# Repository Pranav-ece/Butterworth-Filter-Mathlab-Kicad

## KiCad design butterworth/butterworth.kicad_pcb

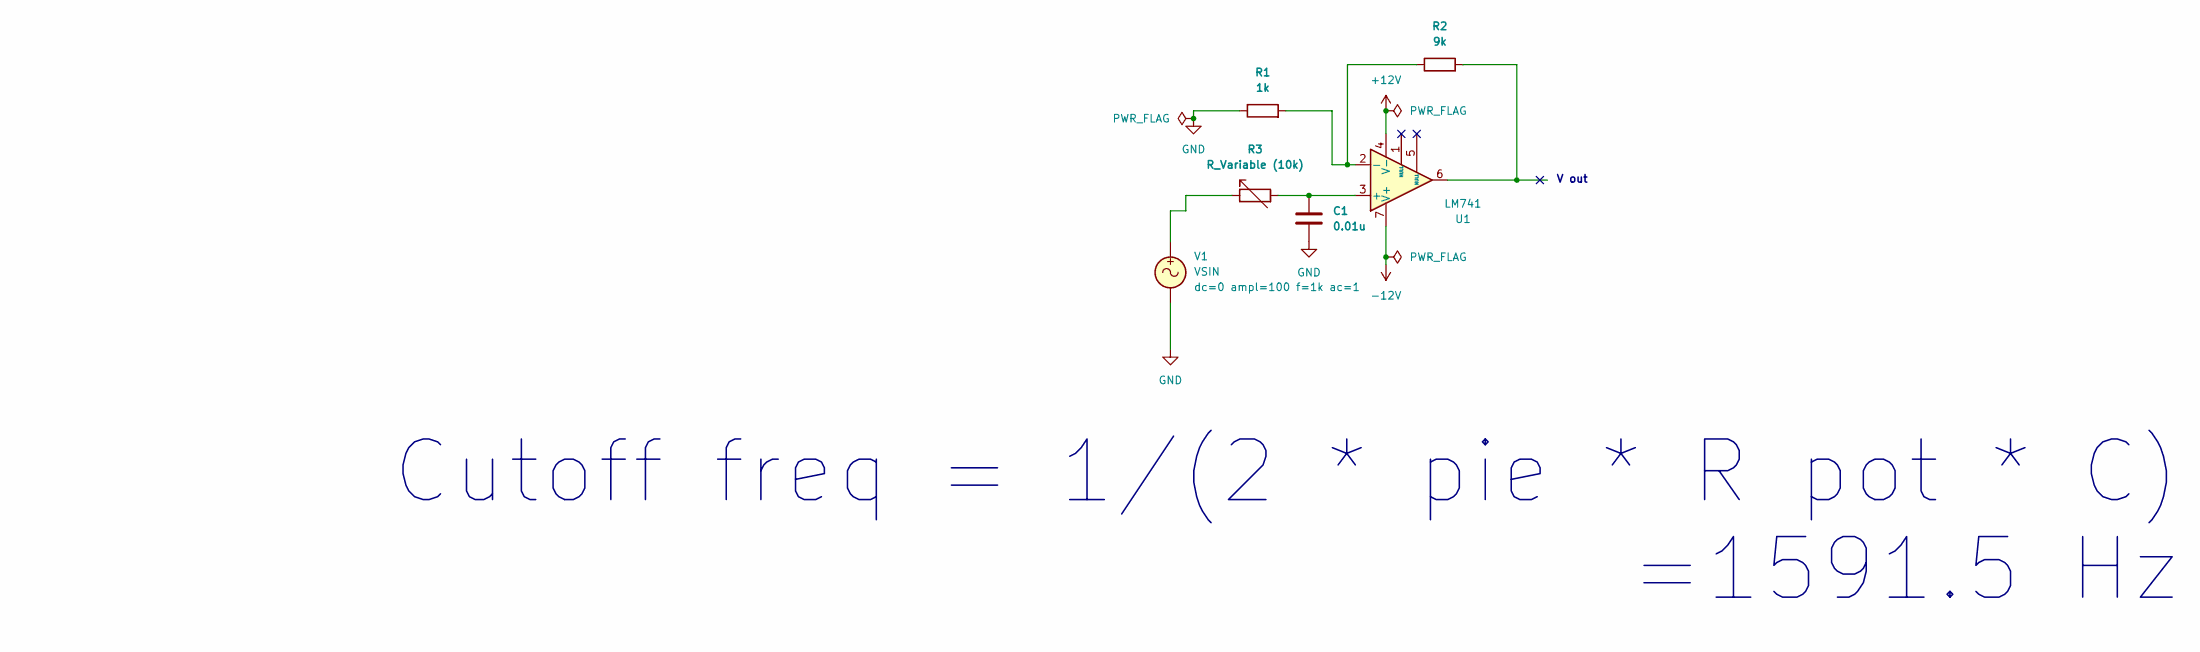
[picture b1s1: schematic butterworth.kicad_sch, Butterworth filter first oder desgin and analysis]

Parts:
C1: 0.01u; CP_Axial_L10.0mm_D4.5mm_P15.00mm_Horizontal
R1: 1k; R_Axial_DIN0204_L3.6mm_D1.6mm_P7.62mm_Horizontal
R2: 9k; R_Axial_DIN0204_L3.6mm_D1.6mm_P7.62mm_Horizontal
R3: R_Variable (10k); Potentiometer_ACP_CA14-VSMD_Vertical_Hole
U1: LM741; CERDIP-8_W7.62mm_SideBrazed_LongPads_Socket
V1: VSIN; CERDIP-8_W7.62mm_SideBrazed

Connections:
+12V: U1.4 (V-)
-12V: U1.7 (V+)
GND: C1.2, R1.1, V1.2
unnamed: R2.2, U1.6
unnamed: R3.1, V1.1
unnamed: C1.1, R3.2, U1.3 (+)
unnamed: R1.2, R2.1, U1.2 (-)

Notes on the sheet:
V out
Cutoff freq = 1/(2 * pie * R pot * C) =1591.5 Hz

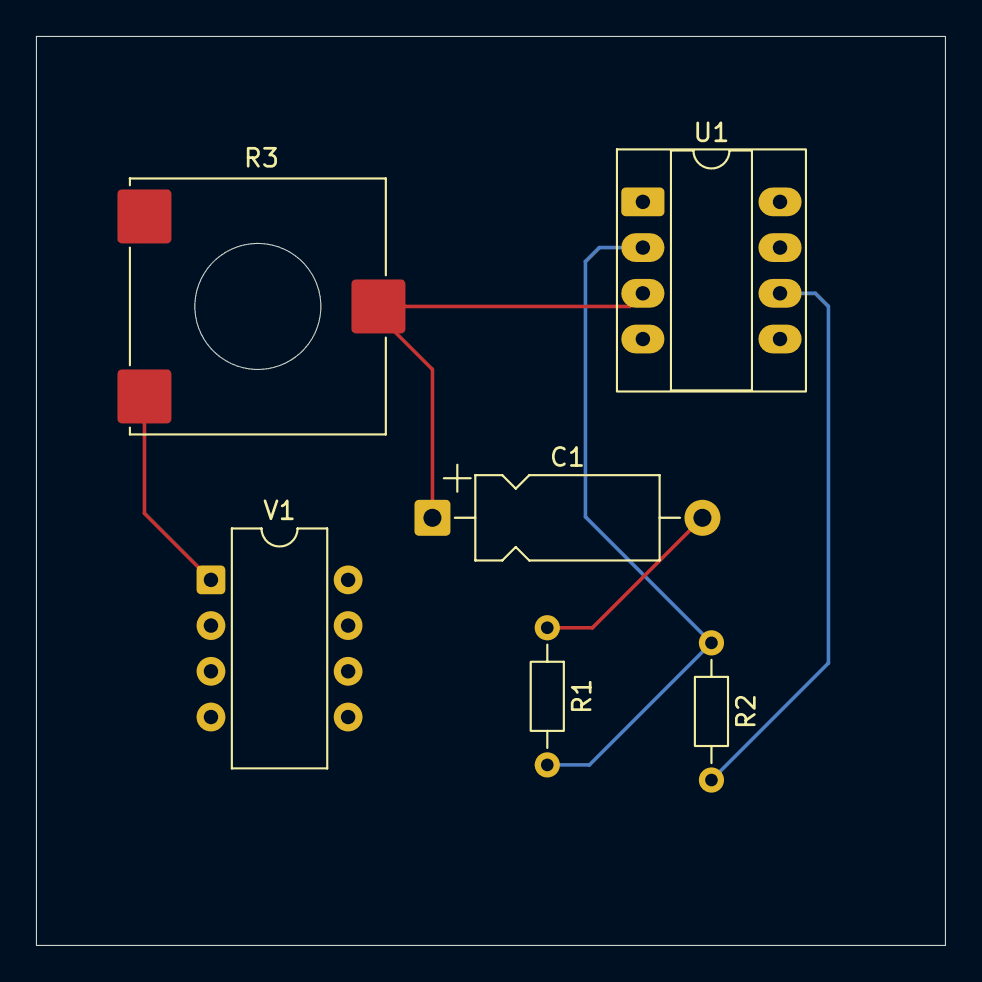
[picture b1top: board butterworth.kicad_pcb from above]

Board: 2 copper layers, 50.5 x 50.5 mm, 6 parts (0 on the bottom side), 5 nets.
